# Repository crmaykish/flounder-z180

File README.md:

# Flounder Z180 Computer

Flounder is a standalone single-board computer built around the Zilog Z180 processor.

It features:
- Clock speed up to 33 MHz (overclockable to 40+)
- 512 KB of both ROM and SRAM
- Two RS-232 serial ports
- 16 GPIO pins
- PS/2 keyboard interface
- Support for 40x4 character LCD display
- CH376S USB storage

## Hardware
An Altera EPM7064 (or EPM7128) 84-pin CPLD provides glue logic and additional interfacing options. An expansion header breaks out address, data, and control lines to support additional hardware development.

## Software
All software development is done in C with the z88dk toolkit. Programs are flashed to and run from the EEPROM.

A hardware monitor program gives access to basic memory and I/O operations including: peek, poke, and memdump.

## Resources
1. [Hackaday Project](https://hackaday.io/project/187588-flounder-z180-sbc)
2. [Z8S180 Datasheet](http://www.zilog.com/docs/z180/z8s180ps.pdf)
3. [z88dk](https://github.com/z88dk/z88dk)

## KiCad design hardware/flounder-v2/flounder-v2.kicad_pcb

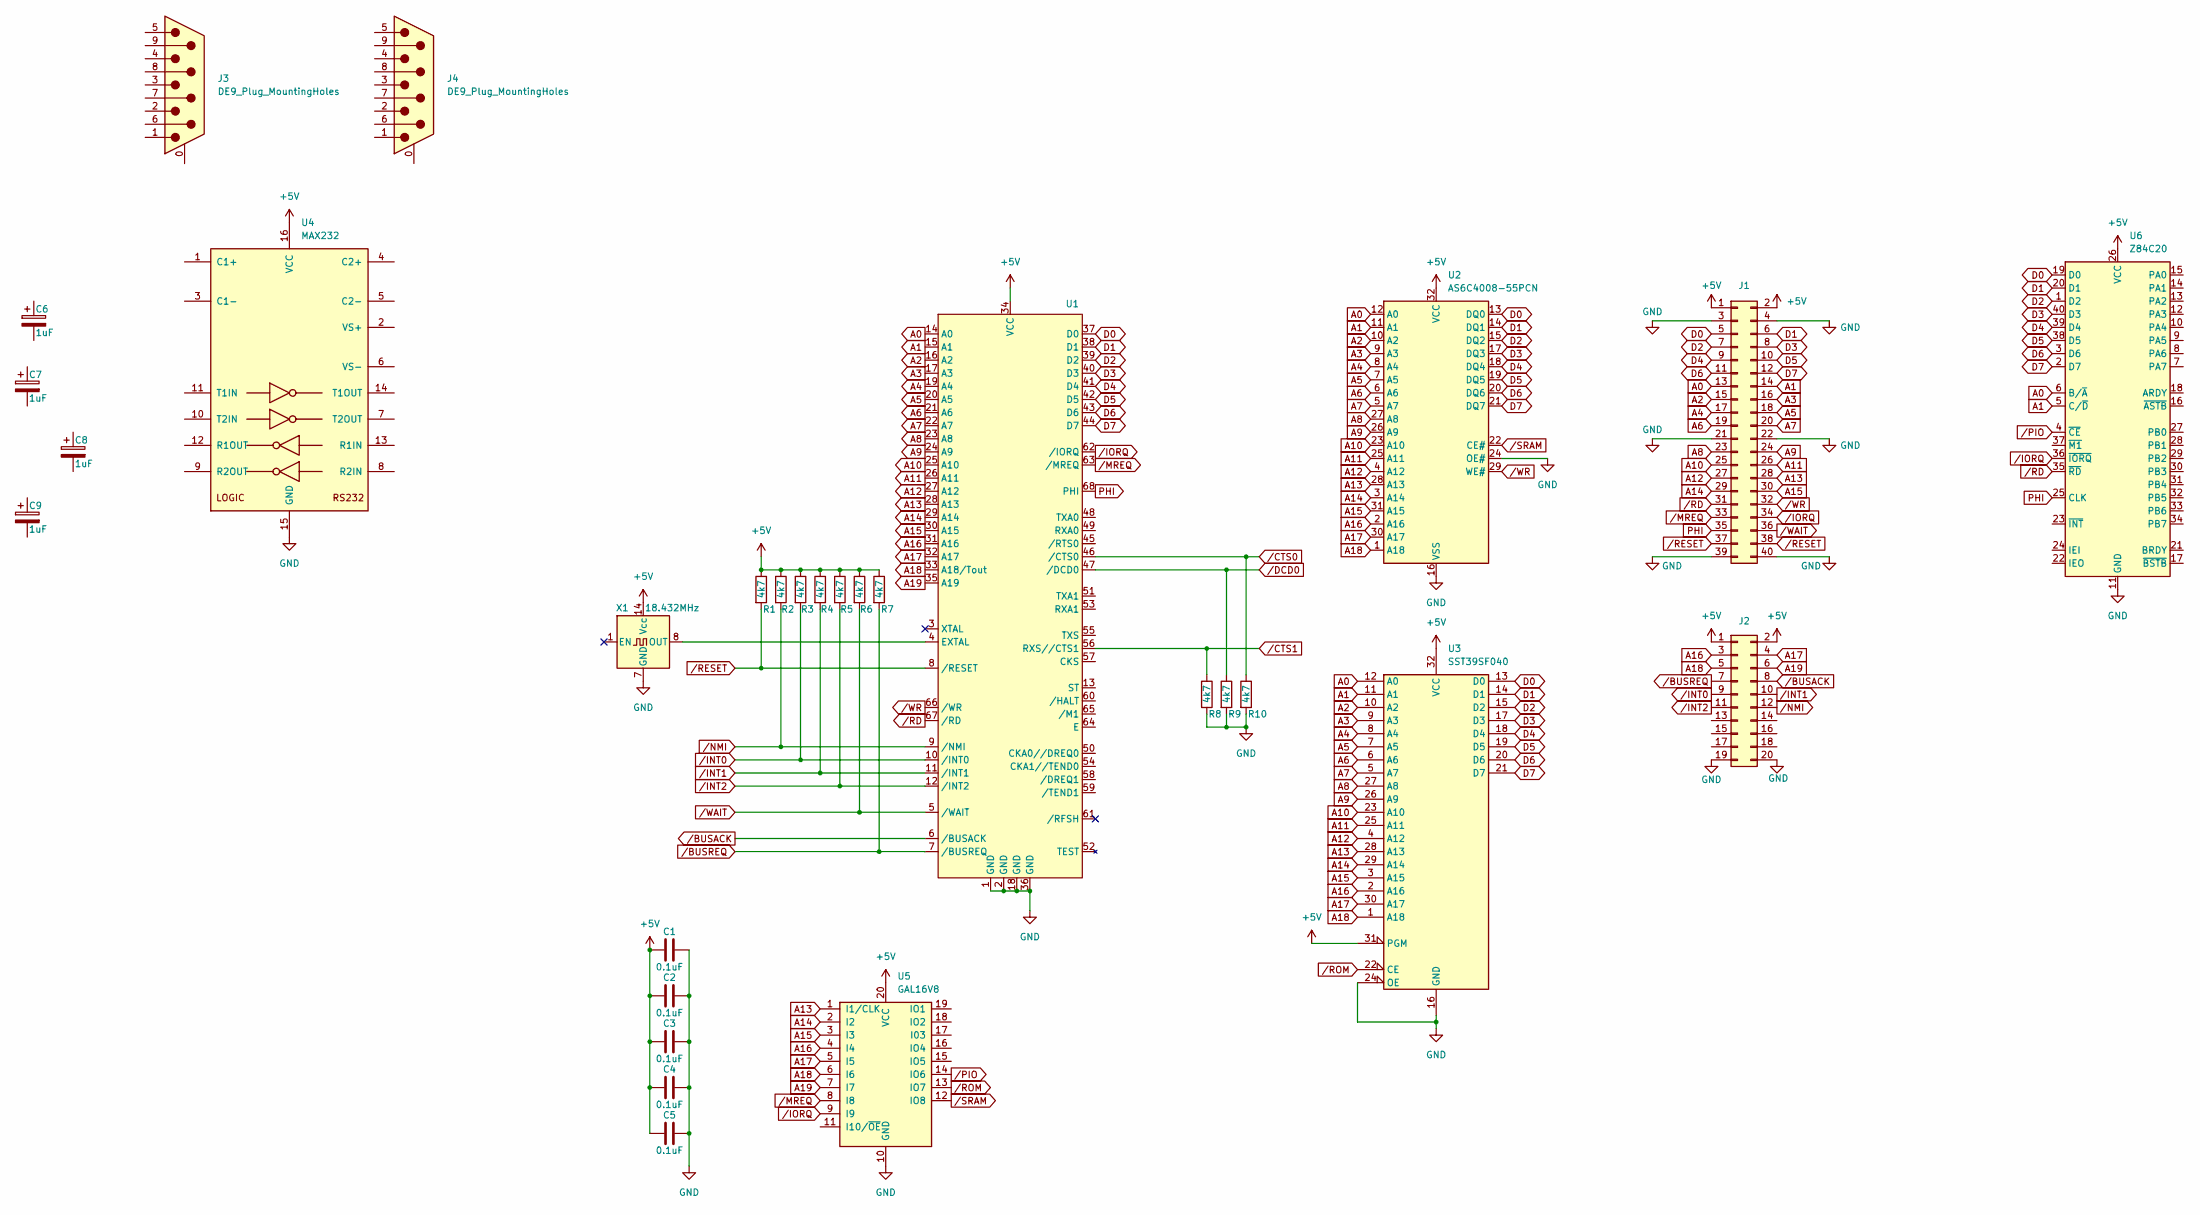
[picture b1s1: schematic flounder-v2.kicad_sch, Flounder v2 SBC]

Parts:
C1, C2, C3, C4, C5: 0.1uF; C_Disc_D5.0mm_W2.5mm_P5.00mm
C6, C7, C8, C9: 1uF; CP_Radial_D5.0mm_P2.50mm
J1: Conn_02x20_Odd_Even; PinHeader_2x20_P2.54mm_Vertical
J2: Conn_02x10_Odd_Even; PinHeader_2x10_P2.54mm_Vertical
J3, J4: DE9_Plug_MountingHoles; DSUB-9_Male_Horizontal_P2.77x2.84mm_EdgePinOffset7.70mm_Hou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
R1, R2, R3, R4, R5, R6, R7, R8, R9, R10: 4k7; R_Axial_DIN0207_L6.3mm_D2.5mm_P7.62mm_Horizontal
U1: Z8S180; PLCC-68_THT-Socket
U2: AS6C4008-55PCN; DIP-32_W15.24mm_Socket
U3: SST39SF040; DIP-32_W15.24mm_Socket
U4: MAX232; DIP-16_W7.62mm_Socket
U5: GAL16V8; DIP-20_W7.62mm_Socket
U6: Z84C20; DIP-40_W15.24mm_Socket
X1: 18.432MHz; Oscillator_DIP-14

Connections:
+5V: C1.1, C2.1, C3.1, C4.1, C5.1, J1.1, J1.2, J2.1, J2.2, R1.1, R2.1, R3.1, R4.1, R5.1, R6.1, R7.1, U1.34 (VCC), U2.32 (VCC), U3.31 (PGM), U3.32 (VCC), U4.16 (VCC), U5.20 (VCC), U6.26 (VCC), X1.14 (Vcc)
A0: J1.13, U1.14 (A0), U2.12 (A0), U3.12 (A0), U6.6 (B/~A)
A1: J1.14, U1.15 (A1), U2.11 (A1), U3.11 (A1), U6.5 (C/~D)
A2: J1.15, U1.16 (A2), U2.10 (A2), U3.10 (A2)
A3: J1.16, U1.17 (A3), U2.9 (A3), U3.9 (A3)
A4: J1.17, U1.19 (A4), U2.8 (A4), U3.8 (A4)
A5: J1.18, U1.20 (A5), U2.7 (A5), U3.7 (A5)
A6: J1.19, U1.21 (A6), U2.6 (A6), U3.6 (A6)
A7: J1.20, U1.22 (A7), U2.5 (A7), U3.5 (A7)
A8: J1.23, U1.23 (A8), U2.27 (A8), U3.27 (A8)
A9: J1.24, U1.24 (A9), U2.26 (A9), U3.26 (A9)
A10: J1.25, U1.25 (A10), U2.23 (A10), U3.23 (A10)
A11: J1.26, U1.26 (A11), U2.25 (A11), U3.25 (A11)
A12: J1.27, U1.27 (A12), U2.4 (A12), U3.4 (A12)
A13: J1.28, U1.28 (A13), U2.28 (A13), U3.28 (A13), U5.1 (I1/CLK)
A14: J1.29, U1.29 (A14), U2.3 (A14), U3.29 (A14), U5.2 (I2)
A15: J1.30, U1.30 (A15), U2.31 (A15), U3.3 (A15), U5.3 (I3)
A16: J2.3, U1.31 (A16), U2.2 (A16), U3.2 (A16), U5.4 (I4)
A17: J2.4, U1.32 (A17), U2.30 (A17), U3.30 (A17), U5.5 (I5)
A18: J2.5, U1.33 (A18/Tout), U2.1 (A18), U3.1 (A18), U5.6 (I6)
A19: J2.6, U1.35 (A19), U5.7 (I7)
D0: J1.5, U1.37 (D0), U2.13 (DQ0), U3.13 (D0), U6.19 (D0)
D1: J1.6, U1.38 (D1), U2.14 (DQ1), U3.14 (D1), U6.20 (D1)
D2: J1.7, U1.39 (D2), U2.15 (DQ2), U3.15 (D2), U6.1 (D2)
D3: J1.8, U1.40 (D3), U2.17 (DQ3), U3.17 (D3), U6.40 (D3)
D4: J1.9, U1.41 (D4), U2.18 (DQ4), U3.18 (D4), U6.39 (D4)
D5: J1.10, U1.42 (D5), U2.19 (DQ5), U3.19 (D5), U6.38 (D5)
D6: J1.11, U1.43 (D6), U2.20 (DQ6), U3.20 (D6), U6.3 (D6)
D7: J1.12, U1.44 (D7), U2.21 (DQ7), U3.21 (D7), U6.2 (D7)
GND: C1.2, C2.2, C3.2, C4.2, C5.2, J1.3, J1.4, J1.21, J1.22, J1.39, J1.40, J2.19, J2.20, R8.2, R9.2, R10.2, U1.1 (GND), U1.2 (GND), U1.18 (GND), U1.36 (GND), U2.16 (VSS), U2.24 (OE#), U3.16 (GND), U3.24 (OE), U4.15 (GND), U5.10 (GND), U6.11 (GND), X1.7 (GND)
unnamed: U1.4 (EXTAL), X1.8 (OUT)
PHI: J1.35, U1.68 (PHI), U6.25 (CLK)
/BUSACK: J2.8, U1.6 (/BUSACK)
/BUSREQ: J2.7, R7.2, U1.7 (/BUSREQ)
/CTS0: R10.1, U1.46 (/CTS0)
/CTS1: R8.1, U1.56 (RXS//CTS1)
/DCD0: R9.1, U1.47 (/DCD0)
/INT0: J2.9, R3.2, U1.10 (/INT0)
/INT1: J2.10, R4.2, U1.11 (/INT1)
/INT2: J2.11, R5.2, U1.12 (/INT2)
/IORQ: J1.34, U1.62 (/IORQ), U5.9 (I9), U6.36 (~IORQ)
/MREQ: J1.33, U1.63 (/MREQ), U5.8 (I8)
/NMI: J2.12, R2.2, U1.9 (/NMI)
/PIO: U5.14 (IO6), U6.4 (~CE)
/RD: J1.31, U1.67 (/RD), U6.35 (~RD)
/RESET: J1.37, J1.38, R1.2, U1.8 (/RESET)
/ROM: U3.22 (CE), U5.13 (IO7)
/SRAM: U2.22 (CE#), U5.12 (IO8)
/WAIT: J1.36, R6.2, U1.5 (/WAIT)
/WR: J1.32, U1.66 (/WR), U2.29 (WE#)

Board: 2 copper layers, 30 parts (0 on the bottom side), 50 nets, no tracks yet.

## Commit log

2021-11-23 Low speed ROM emulation using the Pi Pico
2021-11-23 Add first schematic diagram
2021-11-23 Rewired board without level shifters
2021-11-23 Pi Pico is emulating memory writes
2021-11-23 Reading and writing to Z180 internal registers
2021-11-26 Option to run memory emulation at full speed
2021-11-26 Sending static characters over ASCI
2021-11-26 More UART testing
2021-11-29 Internal UART running at 115200 baud at with 100 kHz clock source
2021-11-29 RAM writes emulated with Pico
2021-11-29 Writing serial bytes from C code!
2021-11-29 Remove old assembly code
2021-11-30 Prime numbers test
2021-11-30 Created simple library for Flounder C API
2021-11-30 Added serial input and memdump
2021-12-11 Setup config for 64KB totall memory
2021-12-29 Updated PLD for address decoder
2021-12-30 Removed putc and getc API calls to avoid stdio conflicts
2021-12-30 comments in the crt
2022-08-09 cleaned up monitor program and added memdump params
2022-08-09 Removed bus spy tool
2022-10-02 Address decoder on CPLD
2022-10-02 Project cleanup
2022-10-02 Add load command to monitor
2022-10-02 explicitly set wait states on boot
2022-10-02 Hacky CPLD read code
2022-10-02 memory map the CPLD to 0xC000+
2022-10-03 Proof of concept PS/2 translator in Verilog
2022-10-03 Add CPLD memory read mode to monitor firmware
2022-10-04 Crude PS/2 to ASCII decoding
2022-10-04 Add user LED outputs to CPLD
2022-10-04 Added delay to PS/2 data sampling Verilog
2022-10-04 Connected SRAM write pin directly to CPU /WR
2022-10-05 Proof of concept PIO output
2022-10-05 Move CPLD to I/O address space
2022-10-05 Add peek and poke commands to monitor
2022-10-05 cleanup
2022-10-05 Moved external IO to higher address range
2022-10-06 Cleaned up code structure
2022-10-06 Reset PIO ports on reset
2022-10-06 Rewrote most of the hardware control in C
2022-10-06 Add ipeek and ipoke to monitor commands
2022-10-06 ASCI0 setup using internal baudrate generator
2022-10-07 Periodic timer interrupts triggered by PRT0
2022-10-08 Hooked up 1602 LCD
2022-10-08 Both segments of the 4004 LCD are functional
2022-10-08 40x4 LCD display moves through all four rows transparently
2022-10-08 Crude vertical scrolling implemented for the LCD display
2022-10-08 Running peek, poke, and clear from LCD
2022-10-09 Interrupts kind of working again
2022-10-09 Interrupts are running, but conflicting with peripherals
2022-10-09 Interrupts fully controlled by z88dk and ISRs in C
2022-10-10 Remove ununsed CRT
2022-10-10 remove VS code settings
2022-10-10 Reinvented ISR
2022-10-10 More wait states, baud rate to 19200
2022-10-10 Add USB decoder to CPLD
2022-10-15 Fix USB enable logic
2022-10-15 Rev 1.0a schematics and gerber files
2022-10-25 Start of decovder for 84 pin CPLD
2022-10-27 Interrupts, ASCI clock, and LCD working on PCB rev 1.0a
2022-10-27 Moved peripheral code to separate files
2022-10-27 Converted build script to makefile
2022-10-27 Bring the readme up to date
2022-10-28 Fixed CPLD conflict with other I/O devices
2022-10-28 CPLD LEDs are now addressable by the CPU
2022-10-28 Loading applications into RAM via the serial port
2022-10-28 Add LCD test to hello program
2022-11-07 Updated timer and CPLD LEDs
2022-11-07 Fix typo
2022-11-07 Properly polling for scancodes
2022-11-07 Moved PS/2 break code handling into PS/2 module
2022-11-08 Add flash command to Makefile
2022-11-08 Monitor now runs with keyboard and LCD only
2022-11-08 Check for 0 characters when reading PS/2 input
2022-11-08 Better picture
2024-08-20 Stubbed out Flounder v2 schematic
2024-08-20 Add PIO to v2
